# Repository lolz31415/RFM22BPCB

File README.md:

RFM22B From HopeRF 2D Footprint and 3D model for use in KiCAD and other software 3D Model created using Fusion 360,
the spacing is very rough, but size of IC, voltage regulator, SMDs,
and Crystal Oscillator are accurate using calipers, other dimensions from the datasheet [here](https://www.sparkfun.com/datasheets/Wireless/General/RFM22.PDF) followed as well.
Schematic Symbol, PCB Layout, and 3D Model for the RFM22B Are shown below and included in this Repository 
The step file is (obviously) the 3D model of the development board/module, "PersonalSymbolsBuilt.kicad_sym" is the library for part, and the folder "PersonalFootprintsBuilt.pretty" contains the footprint for the RFM22B.

Hope this helps someone, someday!

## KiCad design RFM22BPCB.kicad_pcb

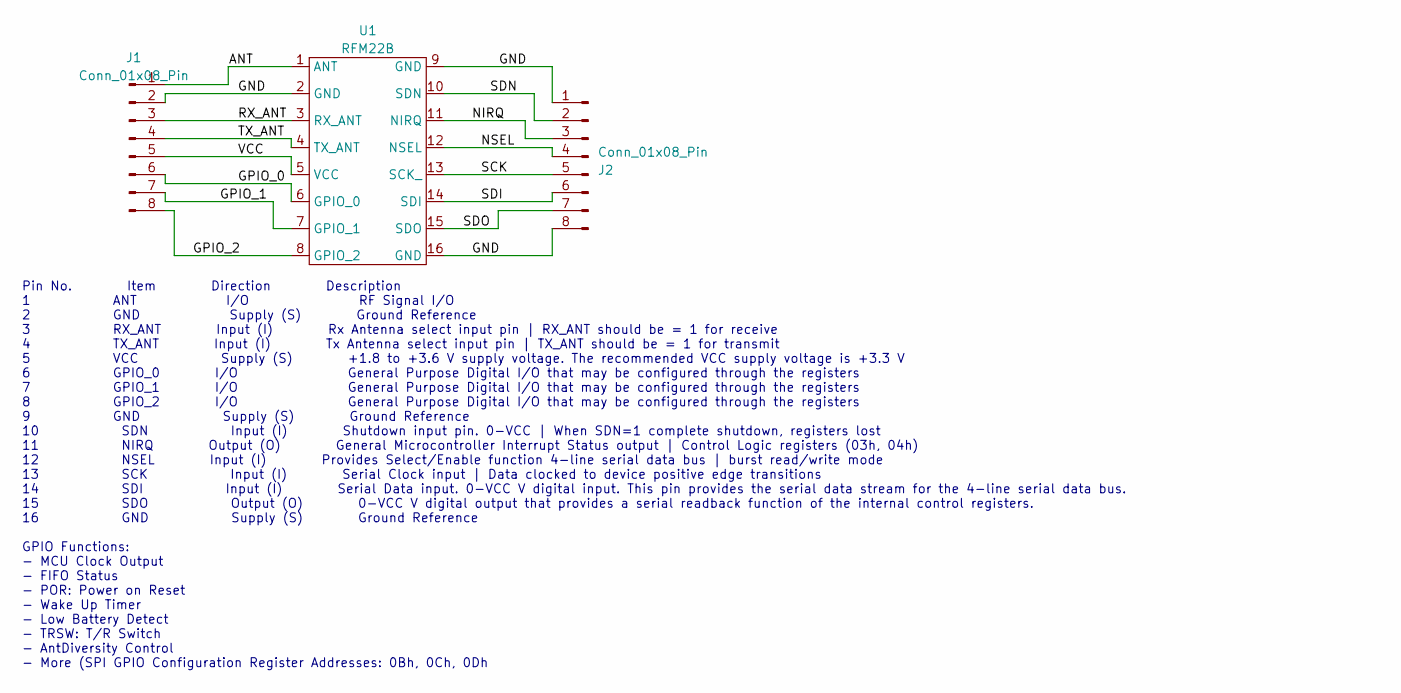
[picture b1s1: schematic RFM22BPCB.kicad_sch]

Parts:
J1, J2: Conn_01x08_Pin; PinHeader_1x08_P2.54mm_Vertical
U1: RFM22B

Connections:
/ANT: J1.1, U1.1 (ANT)
/GND: J1.2, J2.1, J2.8, U1.2 (GND), U1.9 (GND), U1.16 (GND)
/GPIO_0: J1.6, U1.6 (GPIO_0)
/GPIO_1: J1.7, U1.7 (GPIO_1)
/GPIO_2: J1.8, U1.8 (GPIO_2)
/NIRQ: J2.3, U1.11 (NIRQ)
/NSEL: J2.4, U1.12 (NSEL)
/RX_ANT: J1.3, U1.3 (RX_ANT)
/SCK: J2.5, U1.13 (SCK_)
/SDI: J2.6, U1.14 (SDI)
/SDN: J2.2, U1.10 (SDN)
/SDO: J2.7, U1.15 (SDO)
/TX_ANT: J1.4, U1.4 (TX_ANT)
/VCC: J1.5, U1.5 (VCC)

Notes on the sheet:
Pin No. Item Direction Description 1 ANT I/O RF Signal I/O 2 GND Supply (S) Ground Reference 3 RX_ANT Input (I) Rx Antenna select input pin | RX_ANT should be = 1 for receive 4 TX_ANT Input (I) Tx Antenna select input pin | TX_ANT should be = 1 for transmit 5 VCC Supply (S) +1.8 to +3.6 V supply vo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

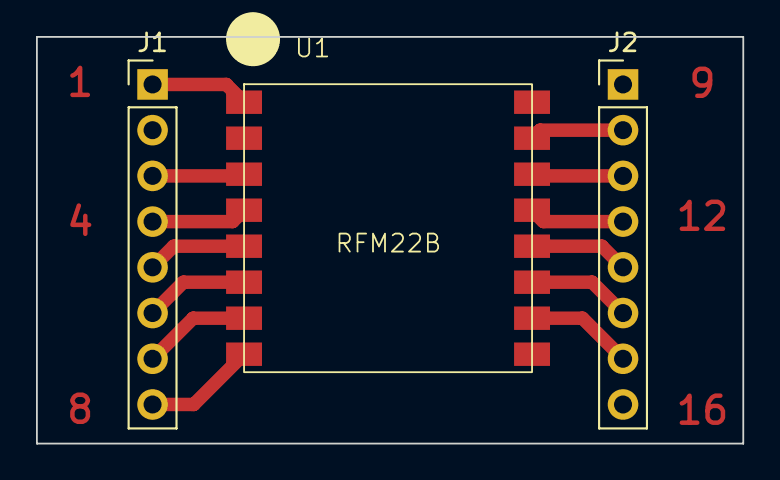
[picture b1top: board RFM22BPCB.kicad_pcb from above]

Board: 2 copper layers, 39.2 x 22.6 mm, 3 parts (0 on the bottom side), 14 nets.

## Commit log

2024-04-10 Symbol, Footprint, & 3D Model of the Part to use
